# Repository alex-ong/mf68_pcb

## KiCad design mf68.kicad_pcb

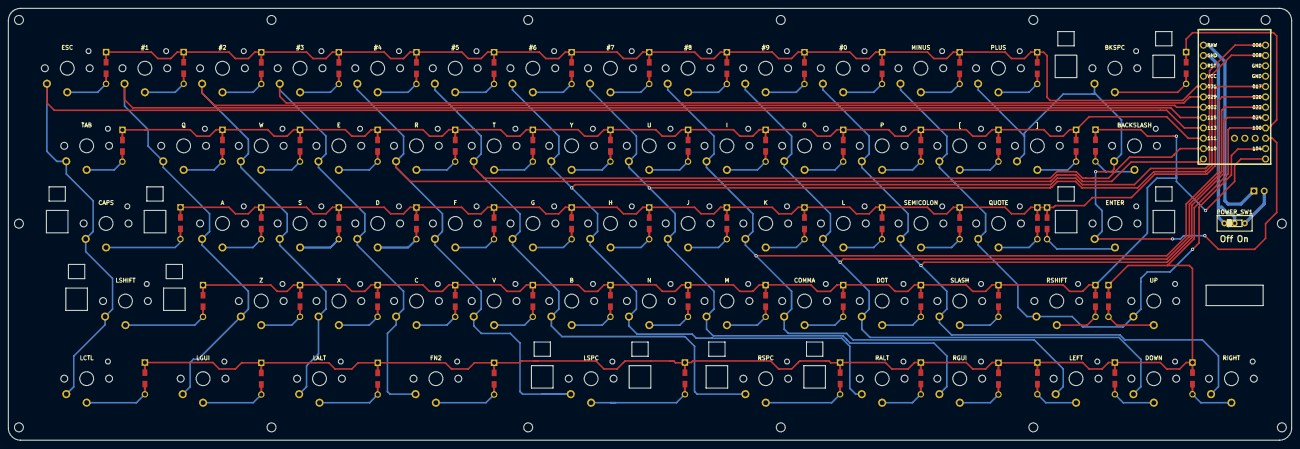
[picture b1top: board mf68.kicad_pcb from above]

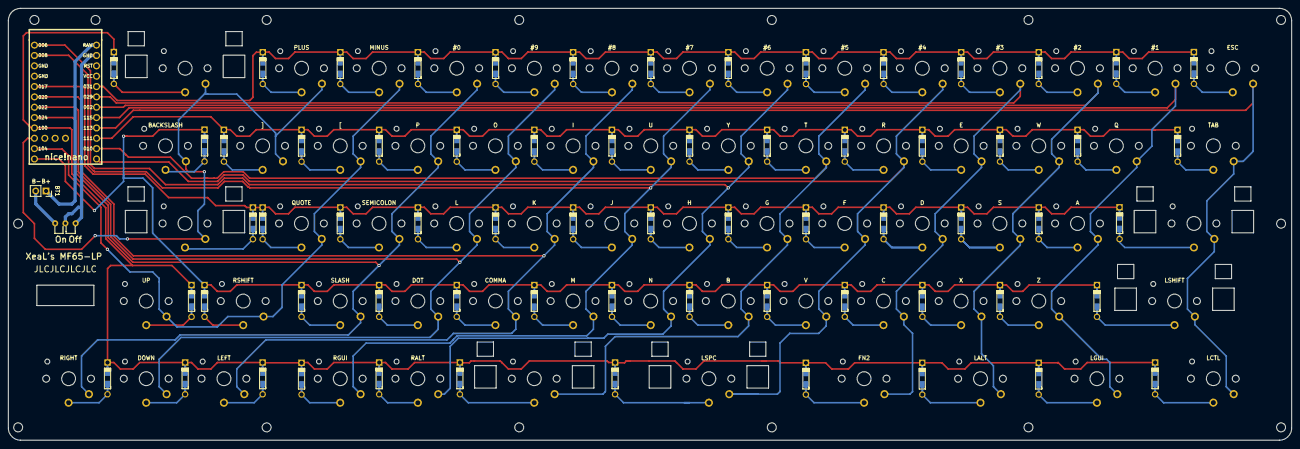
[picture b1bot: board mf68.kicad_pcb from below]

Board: 2 copper layers, 315.0 x 106.0 mm, 133 parts (67 on the bottom side), 86 nets.

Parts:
BT1: Battery; PinSocket_1x02_P2.54mm_Vertical
D1, D2, D3, D4, D5, D6, D7, D8, D9, D10, D11, D12, D13, D14, D15, D16, D17, D18, D19, D20, D21, D22, D23, D24, D25, D26, D27, D28, D29, D30, D31, D32, D33, D34, D35, D36, D37, D38, D39, D40, D41, D42, D43, D44, D45, D46, D47, D48, D49, D50, D51, D52, D53, D54, D55, D56, D57, D58, D59, D60, D61, D62, D63, D64, D65: D; Diode-dual
K1: ESC; Kailh-PG1350-1u-NoLED
K2: #1; Kailh-PG1350-1u-NoLED
K3: #2; Kailh-PG1350-1u-NoLED
K4: #3; Kailh-PG1350-1u-NoLED
K5: #4; Kailh-PG1350-1u-NoLED
K6: #5; Kailh-PG1350-1u-NoLED
K7: #6; Kailh-PG1350-1u-NoLED
K8: #7; Kailh-PG1350-1u-NoLED
K9: #8; Kailh-PG1350-1u-NoLED
K10: #9; Kailh-PG1350-1u-NoLED
K11: #0; Kailh-PG1350-1u-NoLED
K12: MINUS; Kailh-PG1350-1u-NoLED
K13: PLUS; Kailh-PG1350-1u-NoLED
K14: TAB; Kailh-PG1350-1.5u-NoLED
K15: Q; Kailh-PG1350-1u-NoLED
K16: W; Kailh-PG1350-1u-NoLED
K17: E; Kailh-PG1350-1u-NoLED
K18: R; Kailh-PG1350-1u-NoLED
K19: T; Kailh-PG1350-1u-NoLED
K20: Y; Kailh-PG1350-1u-NoLED
K21: U; Kailh-PG1350-1u-NoLED
K22: I; Kailh-PG1350-1u-NoLED
K23: O; Kailh-PG1350-1u-NoLED
K24: P; Kailh-PG1350-1u-NoLED
K25: [; Kailh-PG1350-1u-NoLED
K26: ]; Kailh-PG1350-1u-NoLED
K27: CAPS; Kailh-PG1350-2u-NoLED
K28: A; Kailh-PG1350-1u-NoLED
K29: S; Kailh-PG1350-1u-NoLED
K30: D; Kailh-PG1350-1u-NoLED
K31: F; Kailh-PG1350-1u-NoLED
K32: G; Kailh-PG1350-1u-NoLED
K33: H; Kailh-PG1350-1u-NoLED
K34: J; Kailh-PG1350-1u-NoLED
K35: K; Kailh-PG1350-1u-NoLED
K36: L; Kailh-PG1350-1u-NoLED
K37: SEMICOLON; Kailh-PG1350-1u-NoLED
K38: QUOTE; Kailh-PG1350-1u-NoLED
K39: ENTER; Kailh-PG1350-2u-NoLED
K40: LSHIFT; Kailh-PG1350-2.5u-NoLED
K41: Z; Kailh-PG1350-1u-NoLED
K42: X; Kailh-PG1350-1u-NoLED
K43: C; Kailh-PG1350-1u-NoLED
K44: V; Kailh-PG1350-1u-NoLED
K45: B; Kailh-PG1350-1u-NoLED
K46: N; Kailh-PG1350-1u-NoLED
K47: M; Kailh-PG1350-1u-NoLED
K48: COMMA; Kailh-PG1350-1u-NoLED
K49: DOT; Kailh-PG1350-1u-NoLED
K50: SLASH; Kailh-PG1350-1u-NoLED
K51: RSHIFT; Kailh-PG1350-1.5u-NoLED
K52: BACKSLASH; Kailh-PG1350-1.5u-NoLED
K53: LCTL; Kailh-PG1350-1.5u-NoLED
K54: LGUI; Kailh-PG1350-1.5u-NoLED
K55: LALT; Kailh-PG1350-1.5u-NoLED
K56: FN2; Kailh-PG1350-1.5u-NoLED
K57: LSPC; Kailh-PG1350-2.5u-NoLED
K58: RSPC; Kailh-PG1350-2u-NoLED
K59: RALT; Kailh-PG1350-1u-NoLED
K60: RGUI; Kailh-PG1350-1u-NoLED
K61: LEFT; Kailh-PG1350-1u-NoLED
K62: DOWN; Kailh-PG1350-1u-NoLED
K63: RIGHT; Kailh-PG1350-1u-NoLED
K64: UP; Kailh-PG1350-1u-NoLED
K65: BKSPC; Kailh-PG1350-2u-NoLED
POWER_SW1: SW_SPDT; SS12D00
U1: nice_nano

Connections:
unnamed: BT1.1, U1.24
unnamed: BT1.2, POWER_SW1.3
unnamed: D1.2, K1.1
unnamed: D2.2, K2.1
unnamed: D3.2, K3.1
unnamed: D4.2, K4.1
unnamed: D5.2, K5.1
unnamed: D6.2, K6.1
unnamed: D7.2, K7.1
unnamed: D8.2, K8.1
unnamed: D9.2, K9.1
unnamed: D10.2, K10.1
unnamed: D11.2, K11.1
unnamed: D12.2, K12.1
unnamed: D13.2, K13.1
unnamed: D14.2, K14.1
unnamed: D15.2, K15.1
unnamed: D16.2, K16.1
unnamed: D17.2, K17.1
unnamed: D18.2, K18.1
unnamed: D19.2, K19.1
unnamed: D20.2, K20.1
unnamed: D21.2, K21.1
unnamed: D22.2, K22.1
unnamed: D23.2, K23.1
unnamed: D24.2, K24.1
unnamed: D25.2, K25.1
unnamed: D26.2, K26.1
unnamed: D27.2, K27.1
unnamed: D28.2, K28.1
unnamed: D29.2, K29.1
unnamed: D30.2, K30.1
unnamed: D31.2, K31.1
unnamed: D32.2, K32.1
unnamed: D33.2, K33.1
unnamed: D34.2, K34.1
unnamed: D35.2, K35.1
unnamed: D36.2, K36.1
unnamed: D37.2, K37.1
unnamed: D38.2, K38.1
unnamed: D39.2, K39.1
unnamed: D40.2, K40.1
unnamed: D41.2, K41.1
unnamed: D42.2, K42.1
unnamed: D43.2, K43.1
unnamed: D44.2, K44.1
unnamed: D45.2, K45.1
unnamed: D46.2, K46.1
unnamed: D47.2, K47.1
unnamed: D48.2, K48.1
unnamed: D49.2, K49.1
unnamed: D50.2, K50.1
unnamed: D51.2, K51.1
unnamed: D52.2, K52.1
unnamed: D53.2, K53.1
unnamed: D54.2, K54.1
unnamed: D55.2, K55.1
unnamed: D56.2, K56.1
unnamed: D57.2, K57.1
unnamed: D58.2, K58.1
unnamed: D59.2, K59.1
unnamed: D60.2, K60.1
unnamed: D61.2, K61.1
unnamed: D62.2, K62.1
unnamed: D63.2, K63.1
unnamed: D64.2, K64.1
unnamed: D65.2, K65.1
unnamed: POWER_SW1.1, POWER_SW1.2, U1.23
col0: K1.2, K14.2, K27.2, K40.2, K53.2, U1.16
col1: K2.2, K15.2, K28.2, K41.2, K54.2, U1.17
col2: K3.2, K16.2, K29.2, K42.2, K55.2, U1.18
col3: K4.2, K17.2, K30.2, K43.2, K56.2, U1.19
col4: K5.2, K18.2, K31.2, K44.2, K57.2, U1.13
col5: K6.2, K19.2, K32.2, K45.2, K58.2, U1.14
col6: K7.2, K20.2, K33.2, K46.2, K59.2, U1.1
col7: K8.2, K21.2, K34.2, K47.2, K60.2, U1.2
col8: K9.2, K22.2, K35.2, K48.2, K61.2, U1.6
col9: K10.2, K23.2, K36.2, K49.2, K62.2, U1.7
col10: K11.2, K24.2, K37.2, K50.2, K63.2, U1.8
col11: K12.2, K25.2, K38.2, K51.2, K64.2, U1.11
col12: K13.2, K26.2, K39.2, K52.2, K65.2, U1.10
row0: D1.1, D2.1, D3.1, D4.1, D5.1, D6.1, D7.1, D8.1, D9.1, D10.1, D11.1, D12.1, D13.1, U1.20
row1: D14.1, D15.1, D16.1, D17.1, D18.1, D19.1, D20.1, D21.1, D22.1, D23.1, D24.1, D25.1, D26.1, U1.15
row2: D27.1, D28.1, D29.1, D30.1, D31.1, D32.1, D33.1, D34.1, D35.1, D36.1, D37.1, D38.1, D39.1, U1.5
row3: D40.1, D41.1, D42.1, D43.1, D44.1, D45.1, D46.1, D47.1, D48.1, D49.1, D50.1, D51.1, D52.1, U1.12
row4: D53.1, D54.1, D55.1, D56.1, D57.1, D58.1, D59.1, D60.1, D61.1, D62.1, D63.1, D64.1, D65.1, U1.9

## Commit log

2021-11-15 new: Add files
2021-11-15 add keebio components
2021-11-16 Start working on matrix
2021-11-16 Tweak matrix back to 18 pins
2021-11-16 Labeled all keys
2021-11-16 Arranged a large amount of switches
2021-11-18 Wip: row stagger is wrong!
2021-11-18 wip: Row stagger fixed for ansi
2021-11-18 Fixed annotations, Only missing battery dip switch
2021-11-19 new: Add footprint for microswitch and battery
2021-11-19 Update labels on footprints
2021-11-19 Update MCU postion
2021-11-19 Export for jlcpcb
2021-11-19 new: Add 1u and 2u pretty print cutouts
2021-11-19 new: Add mounting points to pcb
2021-11-20 Add border
2021-11-20 Add m2 mounting hole
2021-11-20 Use m2 mounting holes
2021-12-15 new: Rework pcb, remove all traces as keys are now flipped
2021-12-16 Fully connected PCB
2021-12-16 new: Add text
2022-02-09 new: prepare for export to jlcpcb
2022-02-25 new: Upload pcb zip
2022-02-25 Add mini plate
